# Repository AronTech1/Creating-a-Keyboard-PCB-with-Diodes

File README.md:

# Creating-a-Keyboard-PCB-with-Diodes
Mechanical keyboard PCB with Cherry MX style switches, using a standard diode matrix and a Pro Micro controller

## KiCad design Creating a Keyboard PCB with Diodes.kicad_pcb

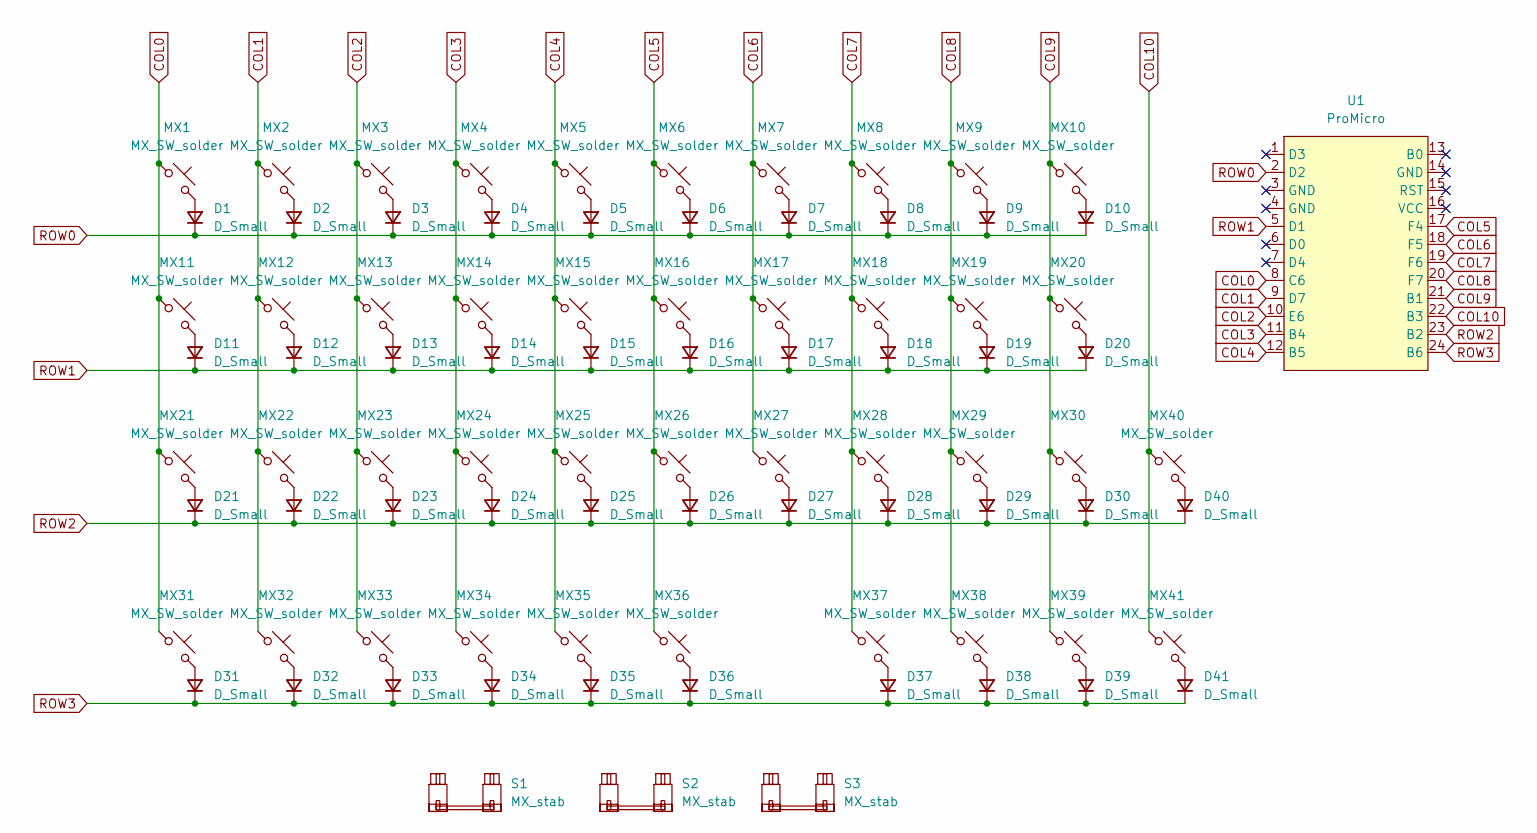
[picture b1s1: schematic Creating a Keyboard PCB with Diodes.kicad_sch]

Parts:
D1, D2, D3, D4, D5, D6, D7, D8, D9, D10, D11, D12, D13, D14, D15, D16, D17, D18, D19, D20, D21, D22, D23, D24, D25, D26, D27, D28, D29, D30, D31, D32, D33, D34, D35, D36, D37, D38, D39, D40, D41: D_Small; D_SOD-123
MX1, MX2, MX3, MX4, MX5, MX6, MX7, MX8, MX9, MX12, MX13, MX14, MX15, MX16, MX17, MX18, MX19, MX22, MX23, MX24, MX25, MX26, MX27, MX28, MX29, MX30, MX32, MX33, MX34, MX35, MX36, MX37, MX38, MX40, MX41: MX_SW_solder; SW_MX_1u
MX10, MX21: MX_SW_solder; SW_MX_1.75u
MX11, MX31, MX39: MX_SW_solder; SW_MX_1.25u
MX20: MX_SW_solder; SW_MX_1.5u
S1: MX_stab; STAB_MX_P_2u
S2: MX_stab; STAB_MX_P_2.25u
S3: MX_stab; STAB_MX_P_6.25u
U1: ProMicro; ProMicro_USBup

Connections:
COL0: MX1.1, MX11.1, MX21.1, MX31.1, U1.8 (C6)
COL1: MX2.1, MX12.1, MX22.1, MX32.1, U1.9 (D7)
COL2: MX3.1, MX13.1, MX23.1, MX33.1, U1.10 (E6)
COL3: MX4.1, MX14.1, MX24.1, MX34.1, U1.11 (B4)
COL4: MX5.1, MX15.1, MX25.1, MX35.1, U1.12 (B5)
COL5: MX6.1, MX16.1, MX26.1, MX36.1, U1.17 (F4)
COL6: MX7.1, MX17.1, MX27.1, U1.18 (F5)
COL7: MX8.1, MX18.1, MX28.1, MX37.1, U1.19 (F6)
COL8: MX9.1, MX19.1, MX29.1, MX38.1, U1.20 (F7)
COL9: MX10.1, MX20.1, MX30.1, MX39.1, U1.21 (B1)
COL10: MX40.1, MX41.1, U1.22 (B3)
unnamed: D1.2 (A), MX1.2
unnamed: D2.2 (A), MX2.2
unnamed: D3.2 (A), MX3.2
unnamed: D4.2 (A), MX4.2
unnamed: D5.2 (A), MX5.2
unnamed: D6.2 (A), MX6.2
unnamed: D7.2 (A), MX7.2
unnamed: D8.2 (A), MX8.2
unnamed: D9.2 (A), MX9.2
unnamed: D10.2 (A), MX10.2
unnamed: D11.2 (A), MX11.2
unnamed: D12.2 (A), MX12.2
unnamed: D13.2 (A), MX13.2
unnamed: D14.2 (A), MX14.2
unnamed: D15.2 (A), MX15.2
unnamed: D16.2 (A), MX16.2
unnamed: D17.2 (A), MX17.2
unnamed: D18.2 (A), MX18.2
unnamed: D19.2 (A), MX19.2
unnamed: D20.2 (A), MX20.2
unnamed: D21.2 (A), MX21.2
unnamed: D22.2 (A), MX22.2
unnamed: D23.2 (A), MX23.2
unnamed: D24.2 (A), MX24.2
unnamed: D25.2 (A), MX25.2
unnamed: D26.2 (A), MX26.2
unnamed: D27.2 (A), MX27.2
unnamed: D28.2 (A), MX28.2
unnamed: D29.2 (A), MX29.2
unnamed: D30.2 (A), MX30.2
unnamed: D31.2 (A), MX31.2
unnamed: D32.2 (A), MX32.2
unnamed: D33.2 (A), MX33.2
unnamed: D34.2 (A), MX34.2
unnamed: D35.2 (A), MX35.2
unnamed: D36.2 (A), MX36.2
unnamed: D37.2 (A), MX37.2
unnamed: D38.2 (A), MX38.2
unnamed: D39.2 (A), MX39.2
unnamed: D40.2 (A), MX40.2
unnamed: D41.2 (A), MX41.2
ROW0: D1.1 (K), D2.1 (K), D3.1 (K), D4.1 (K), D5.1 (K), D6.1 (K), D7.1 (K), D8.1 (K), D9.1 (K), D10.1 (K), U1.2 (D2)
ROW1: D11.1 (K), D12.1 (K), D13.1 (K), D14.1 (K), D15.1 (K), D16.1 (K), D17.1 (K), D18.1 (K), D19.1 (K), D20.1 (K), U1.5 (D1)
ROW2: D21.1 (K), D22.1 (K), D23.1 (K), D24.1 (K), D25.1 (K), D26.1 (K), D27.1 (K), D28.1 (K), D29.1 (K), D30.1 (K), D40.1 (K), U1.23 (B2)
ROW3: D31.1 (K), D32.1 (K), D33.1 (K), D34.1 (K), D35.1 (K), D36.1 (K), D37.1 (K), D38.1 (K), D39.1 (K), D41.1 (K), U1.24 (B6)

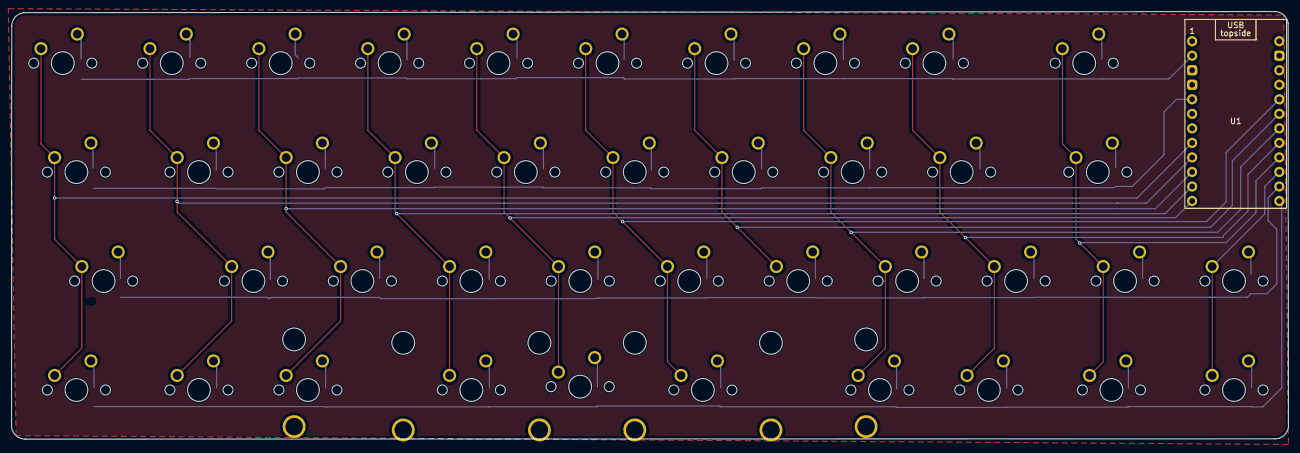
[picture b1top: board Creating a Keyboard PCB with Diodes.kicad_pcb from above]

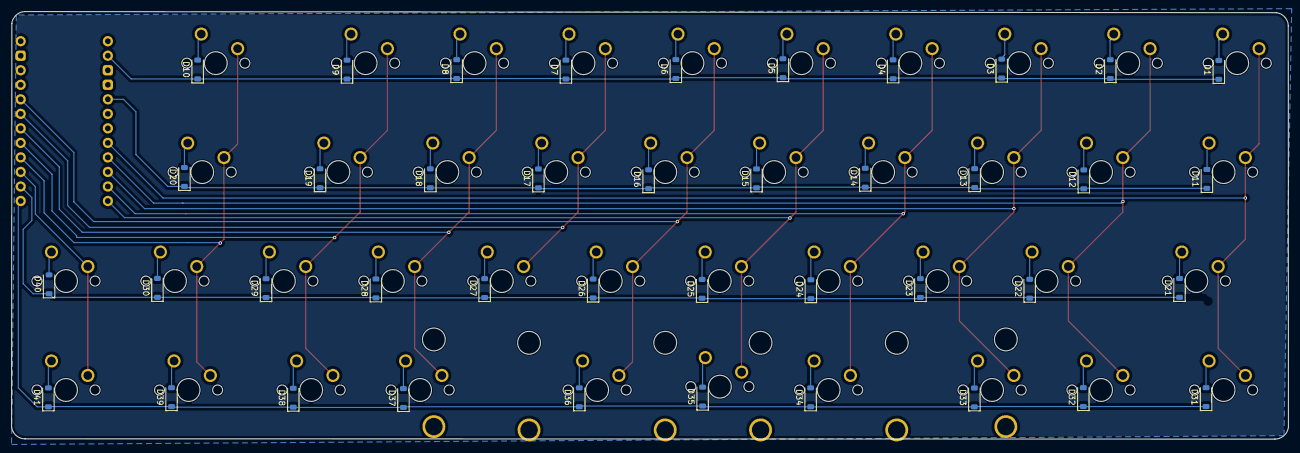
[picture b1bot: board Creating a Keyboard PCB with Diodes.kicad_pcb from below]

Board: 2 copper layers, 223.3 x 74.7 mm, 86 parts (41 on the bottom side), 56 nets.
